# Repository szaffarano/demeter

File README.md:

## Demeter

Controlador de riego que incorpora algunas mejoras con respecto a su predecesor baudino relacionadas con el manejo remoto y ampliación de sensores que maneja.

Está implementado en un microcontrolador AVR ATMega328 **sin bootloeader ni librerías Arduino**.

Versión preliminar con una implementación parcial del protocolo modbus.

### Roadmap

- ~~Terminar de mapear registros modbus a sensores, parámetros y comandos del controlador.~~
- Implementar servicio rest para interactuar remotamente.
- Realizar prueba de concepto para usar NRF24L01+ en lugar del módulo bluetooth.
- ~~Documentar esquemáticos en kicad~~.
- Armar una webapp para administrar el controlador.
- Incorporar interrupción watchdog para preveer posibles fallos.
- Implementar los relays usando triacs+opto.
- Agregar sensor de humedad de tierra.
- Desdoblar los controles para riego tradicional (tierra) e hidropónico en forma independiente.
- Optimizar lógica en los mapeos para ahorrarse algunos ciclos de cpu y memoria.
- Agregar en el cliente python funciones de alto nivel (ej get_date que lea grupo de registros de la fecha en vez de llamar a read_holding_registers).
- ~~Refactorizar mapeo de registros modbus para optimizar bits y que no quede todo en uint16_t.~~ (DUPLICADO).
- Optimizar algoritmo en los callbacks modbus.
- Generar tickets github para no mantener un archivo de pendientes...

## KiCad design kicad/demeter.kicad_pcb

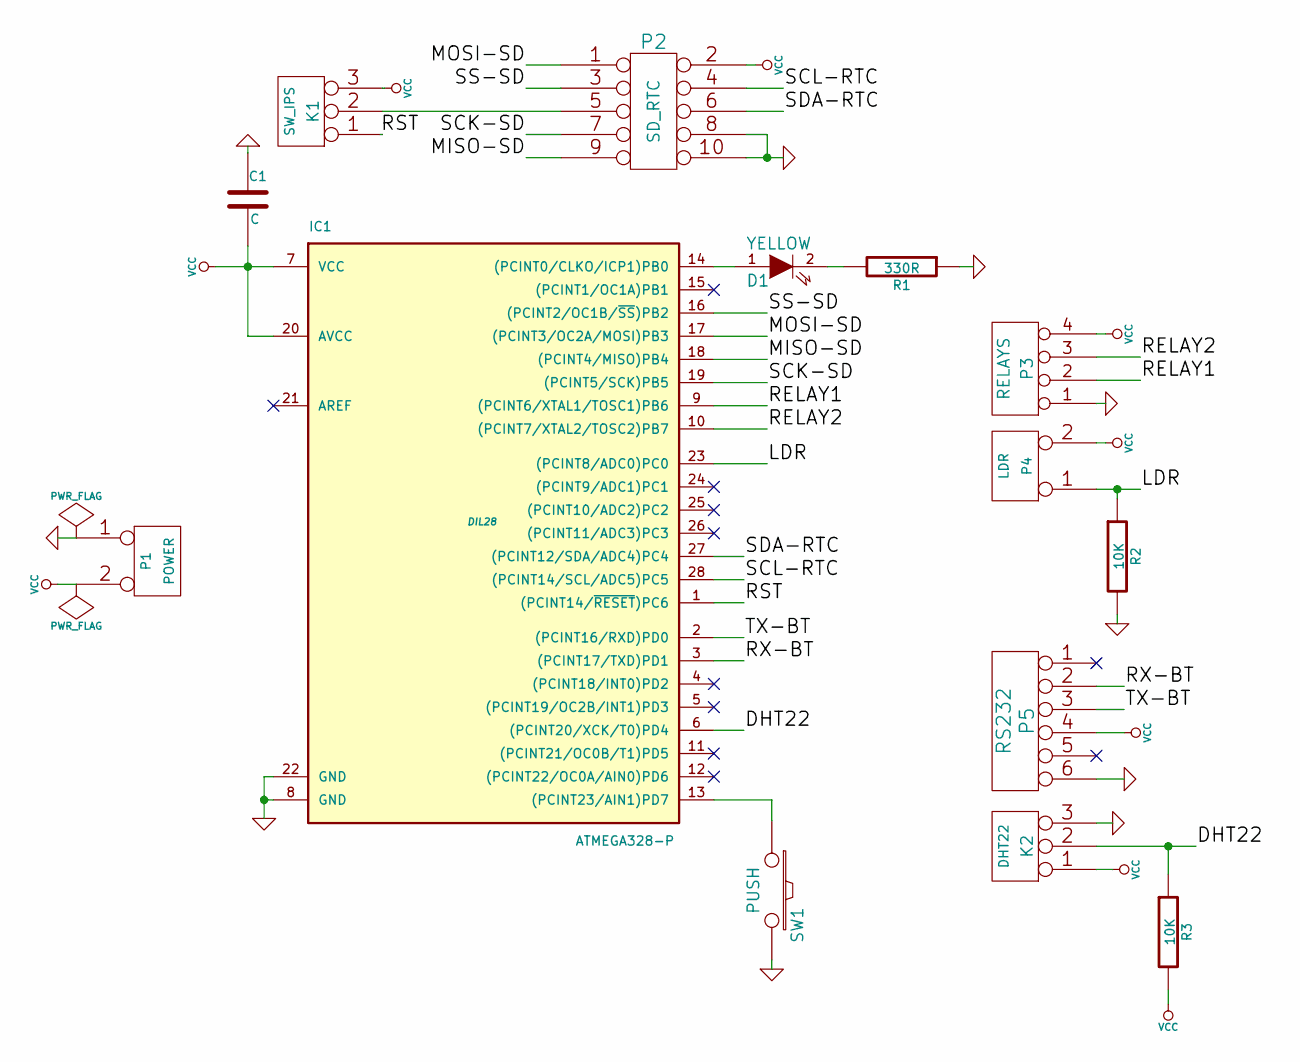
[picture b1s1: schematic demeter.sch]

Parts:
C1: C
D1: YELLOW
IC1: ATMEGA328-P; DIL28
K1: SW_IPS
K2: DHT22
P1: POWER
P2: SD_RTC
P3: RELAYS
P4: LDR
P5: RS232
R1: 330R
R2, R3: 10K
SW1: PUSH

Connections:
/DHT22: IC1.6 ((PCINT20/XCK/T0)PD4), K2.2 (PM), R3.1
/LDR: IC1.23 ((PCINT8/ADC0)PC0), P4.1, R2.1
/MISO-SD: IC1.18 ((PCINT4/MISO)PB4), P2.9
/MOSI-SD: IC1.17 ((PCINT3/OC2A/MOSI)PB3), P2.1
/RELAY1: IC1.9 ((PCINT6/XTAL1/TOSC1)PB6), P3.2
/RELAY2: IC1.10 ((PCINT7/XTAL2/TOSC2)PB7), P3.3
/RST: IC1.1 ((PCINT14/~RESET~)PC6), K1.1
/RX-BT: IC1.3 ((PCINT17/TXD)PD1), P5.2
/SCK-SD: IC1.19 ((PCINT5/SCK)PB5), P2.7
/SCL-RTC: IC1.28 ((PCINT14/SCL/ADC5)PC5), P2.4
/SDA-RTC: IC1.27 ((PCINT12/SDA/ADC4)PC4), P2.6
/SS-SD: IC1.16 ((PCINT2/OC1B/~SS~)PB2), P2.3
/TX-BT: IC1.2 ((PCINT16/RXD)PD0), P5.3
GND: C1.1, IC1.8 (GND), IC1.22 (GND), K2.3, P1.1, P2.8, P2.10, P3.1, P5.6, R1.1, R2.2, SW1.2
unnamed: D1.1 (A), IC1.14 ((PCINT0/CLKO/ICP1)PB0)
unnamed: D1.2 (K), R1.2
unnamed: IC1.13 ((PCINT23/AIN1)PD7), SW1.1
unnamed: K1.2 (PM), P2.5
VCC: C1.2, IC1.7 (VCC), IC1.20 (AVCC), K1.3, K2.1, P1.2 (PM), P2.2, P3.4, P4.2 (PM), P5.4, R3.2

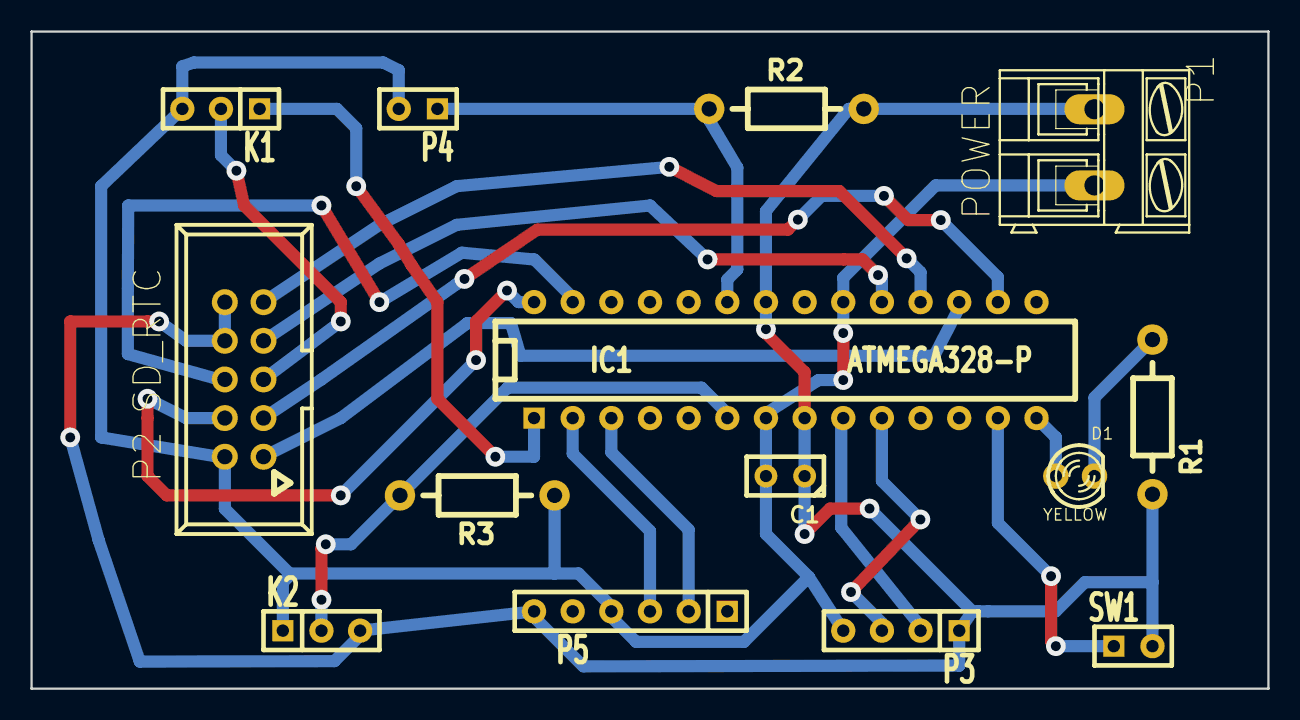
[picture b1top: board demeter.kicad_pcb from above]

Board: 2 copper layers, 81.3 x 43.2 mm, 14 parts (0 on the bottom side), 19 nets.

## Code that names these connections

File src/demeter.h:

/*
 * demeter.h
 *
 *  Created on: 08/06/2014
 *      Author: sebas
 */

#ifndef SANDBOX_H_
#define SANDBOX_H_

#include <rtc/rtc.h>

// Relays
#define  RELAY0			PB6
#define  RELAY0_PORT		PORTB
#define  RELAY0_DDR		DDRB

#define  RELAY1			PB7
#define  RELAY1_PORT		PORTB
#define  RELAY1_DDR		DDRB

// Pulsador
#define  PUSH			PD7
#define  PUSH_PORT		PIND
#define  PUSH_DDR		DDRD

// UART
#define UART_BAUD_RATE		9600

// sensor luminico
#define	PHOTORESISTOR		PC0

#define	LED			PB0
#define	LED_PORT		PORTB
#define LED_DDR			DDRB

// cantidad de eventos que permite parametrizar.
#define	MAX_EVENTS		10

typedef struct _datetime_t {
	int16_t year;
	int16_t month;
	int16_t date;
	int16_t hour;
	int16_t minute;
	int16_t second;
} datetime_t;

typedef struct _state_t {
	int16_t temperature;
	int16_t humidity;
	int16_t light;
} state_t;

typedef struct _instant_t {
	uint16_t hour;
	uint16_t minute;
	uint16_t second;
} instant_t;

// un evento es el cron que indica cuándo activar un relay y por cuánto tiempo.
typedef struct _event_t {
	instant_t start;
	uint16_t duration;
	uint16_t target;
	uint16_t enabled;
} event_t;

#endif /* DEMETER_H_ */

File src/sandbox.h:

/*
 * sandbox.h
 *
 *  Created on: 08/06/2014
 *      Author: sebas
 */

#include <rtc/rtc.h>

#ifndef SANDBOX_H_
#define SANDBOX_H_

// Relays
#define  RELAY1			PD3
#define  RELAY1_PORT	PORTD
#define  RELAY1_DDR		DDRD

#define  RELAY2			PD4
#define  RELAY2_PORT	PORTD
#define  RELAY2_DDR		DDRD

// Pulsador
#define  PUSH			PB1
#define  PUSH_PORT		PINB
#define  PUSH_DDR		DDRB

// UART
#define UART_BAUD_RATE	9600

// sensor luminico
#define	PHOTORESISTOR	PC0

#define	LOG				"clima.log"

#define LED_DDR			DDRB
#define	LED_PORT		PORTB
#define	LED				PB0

#define	MAX_EVENTS		10
// datos

typedef struct _event_t {
	rtc_datetime_24h_t start;
	unsigned int duration;
	uint8_t target;
} event_t;

#endif /* SANDBOX_H_ */

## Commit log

2014-06-07 Versión inicial.
2014-06-07 Agrega macro para simplificar código. Renombra variables para claridad de funcionalidad
2014-06-07 Refactoring de nombres y mueve de lugar macros de uso interno
2014-06-07 Agrega soporte FatFS
2014-06-08 Incorpora librería para interactuar con sensor DHT22
2014-06-08 Incorpora librería para señales analógicas (sensor lumínico)
2014-06-08 Incorpora librería FatFS
2014-06-08 Incorpora librería RTC y dependencía i2c.
2014-06-08 Incorpora librería para manipulación de ports de I/O
2014-06-08 Incorpora librería de temporizadores
2014-06-08 Modificaciones para adaptar a las nuevas librerías.
2014-06-08 Agrego impresión en usart para indicar que se escribe en el log
2014-06-08 Modifica prescaler para oscilador de 8Mhz en lugar del externo de 16 Mhz que se estaba usando
2014-06-12 Agrega binarios al gitignore
2014-06-12 Agrega configuración en EEPROM
2014-06-12 Agrega import que hacia falta
2014-06-12 Agrega métodos para manejar relays
2014-06-12 Incorporo makefile para agilizar construcción
2014-06-12 Incorpora menu muy simple para interactuar con la configuración
2014-06-28 Adapta puertos para utilizar sd en datalogger. Necesario por el temporizador de la libreria ff que se solapaba con temporizador para monitoreo de eventos
2014-06-28 Se pasa a usar temporizador 0, de 8 bits, pues el 1 lo necesita la libreria ff
2014-06-28 Incorpora cliente python para interactuar con modbus
2014-06-28 Agrega libreria modbus como submodulo.
2014-06-28 Modifica puerto
2014-06-28 Mejora en el manejo de configuraciones en eeprom.
2014-06-28 Cambia flag de gcc para omitir warning por libreria ff
2014-06-28 Adapta todo lo hecho con una implementacion muy simple de modbus, resta mejorar el mapeo de registros
2014-06-28 Configuraciones de git
2014-06-28 Eliminacion de libreria que no se usa
2014-06-28 Algo de info
2014-06-28 Borra archivo pyc subido por error e incorpora dichos archivos a gitignore
2014-06-30 Elimina identificador volatile pues ya no es necesario y eso impide optimizaciones del compilador
2014-06-30 Arregla bug con los puertos ya que cuando se redefinieró el port del pulsador quedó desactualizada la inicialización del pin change interrput correspondiente. Agrega funcionalidad al cliente python. 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
2014-07-01 Renombra constantes de delays para comenzar en cero. Cambia semántica de activación de relays para tomar cero como primer relay en vez de uno. Agrega método para informar si presionaron el pulsador (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
2014-07-01 Mejora lógica de manejo de relays.
2014-07-01 Arregla bug en write_coils, cuando se escribía desde una posición mayor a cero.
2014-07-01 Implementa comandos de alto nivel para interactuar con todos los sensores y registros
2014-07-02 Agrega manejo de errores en comandos.
2014-07-02 Mejora formato del log para no loguear boludeces. Incorpora file rolling para evitar que los archivos crezcan indefinidamente (rolea por dia)
2014-07-02 Actualiza pendientes.
2014-07-02 Imagen del prototipo casi finalizado
2014-07-03 Esquemático y netlis
2014-07-03 Corrige indentación
2014-07-03 Agrega archivo de footprints.
2014-07-07 Archivos del pcb
2014-07-07 Esquemáticos Kicad
2014-07-07 Actualia roadmap
2014-07-07 Excluye archivos temporales de kicad
2014-07-07 Fixea bug en validación de parámetros
2014-07-07 Agrega foto con primera aproximación al prototipo en pcb
2014-07-09 Agrega comandos de alto nivel para habilitar/deshabilitar eventos, informar temperatura, humedad y nivel lumínico.
2014-07-09 Agrega en el log información sobre el estado de los relays.
2014-07-09 Fotos del modelo terminado.
2018-09-09 Make script python3 complient
2018-09-09 Make libs platform.io compatible
2018-09-09 Add platform.io configuration
2018-09-09 Change branch in modbus
2018-09-09 Modify includes
2018-09-09 Add argument parser
2018-09-09 Add some english translations
